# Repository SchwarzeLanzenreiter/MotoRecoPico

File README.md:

# MotoRecoPico

A CAN + GPS data logger for motorcycles. A home-made board carrying a **Raspberry Pi Pico 2
(RP2350)** records the vehicle's CAN bus and GPS to a microSD card. The resulting files open
directly in [MotoRecoViewer](https://github.com/SchwarzeLanzenreiter/MotoRecoViewer).

This is [MotoRecoLogger](https://github.com/SchwarzeLanzenreiter/MotoRecoLogger) — which ran on a
Raspberry Pi plus a HAT — collapsed onto a single board. The recording format is compatible, so old
and new logs read with the same tools.

## Repository layout

| Directory | Contents |
|---|---|
| [`firmware/`](firmware/) | Firmware for the Pico 2 (C / pico-sdk). See [firmware/README.md](firmware/README.md) |
| `cad/kicad/` | KiCad 10 project, fabrication data, generation and inspection scripts |
| `cad/electronics/` | The old EAGLE version (reference only; KiCad is current) |
| [`docs/`](docs/) | Design documents. **[netlist.md](docs/netlist.md) is the canonical description of the circuit** |

## Hardware

| Item | Details |
|---|---|
| Board | 4 layers, 21 × 61 mm, 41 components. The only leaded parts are J1, Y1 and the Pico header |
| MCU | Raspberry Pi Pico 2 (RP2350). Replaceable, in a 2×20 socket. Moved to the back side in v4.2 |
| CAN | Microchip MCP25625 (controller and transceiver in one), driven over SPI1 |
| GPS | YIC GT-502MGG-N. NMEA over UART0 at 9600 bps |
| Storage | microSD (Hirose DM3AT-SF-PEJM5) over SPI0 |
| Vehicle I/F | TE MQS .63, 8 way. Only 5 of them are used: permanent 12V, IG, CAN High, CAN Low, GND |
| Power | 12V → AP63205 buck converter → 5V. The 3.3V rail comes from the Pico's 3V3(OUT) |

**Power is held up for about 0.55 s (measured) after the key goes off.** C13 holds the gate charge
of the high-side switch, and the firmware uses that grace period to close the log. The contract is
in [netlist.md](docs/netlist.md) §4.7.

How the design got here — why four layers, why this placement, what each revision fixed — is
recorded in [netlist.md](docs/netlist.md) and [hardware-design.md](docs/hardware-design.md).
Where to buy the parts is in [parts-sourcing.md](docs/parts-sourcing.md).

## Firmware

- Runs as a **single loop**. There are only two interrupts: CAN reception and the GPS UART
- CAN reception is moved into a ring buffer by the interrupt, so the controller's two-stage FIFO
  does not overflow even when an SD write blocks for hundreds of milliseconds
- NMEA is parsed in-house (replacing gpsd on the Pi version). There is no RTC, so GPS time is
  pinned to the monotonic clock
- FatFs R0.16 is bundled. The SPI block driver for the SD card is our own
- A log is finalized **only on IG OFF detection**. CAN engine speed is not used, to keep
  vehicle-specific knowledge out of the firmware
- The time zone is configured through a hidden file `MOTORECO.CFG` on the microSD card (no rebuild)
- The hardware-independent parts (NMEA, encoding, settings, IG decision, clock) **have tests that
  run on a bare Pico 2 or on a PC**

Build instructions, how to read the logs, and troubleshooting are in
[firmware/README.md](firmware/README.md).

## Recording format (`.dat`)

A sequence of fixed-length 16-byte records. No header, no delimiters, everything little-endian.

| Offset | Type | Contents |
|---|---|---|
| 0 | `uint32` | Seconds since the log started |
| 4 | `uint16` | Milliseconds within that second |
| 6 | `uint16` | CAN ID (standard 11-bit) |
| 8 | `uint8[8]` | Payload (zero-padded when DLC is less than 8) |

GPS rides on CAN IDs that cannot exist, as fixed-point values. **`0x7FF`** carries longitude and
latitude, **`0x7FE`** carries altitude and speed. That way CAN and GPS land in one single time
series.

**`0x7FD`** (added for MotoNavi, not written by the Pi version) carries the absolute time of each
fix, since the record time above only counts from the start of the log. One per fix, written when
the fix's GGA sentence arrives and after any `0x7FF` that sentence produced, so it pairs with the
`0x7FF` at or just before it. It is written while standing still too, when `0x7FF` is skipped
because the position has not changed:

| Bytes | Contents |
|---|---|
| 0–5 | UTC of the fix, Unix milliseconds, 48-bit little-endian |
| 6 | Fix kind in the high nibble (0 none, 1 2D, 2 3D, 3 DGPS/SBAS/RTK), satellites used in the low nibble (15 = 15 or more) |
| 7 | HDOP × 10, rounded (255 = 25.5 or more, 0 = not reported) |

The time of day, satellites and HDOP all come from that GGA. GGA has no date, so the date is
taken from the last RMC with a fix, and nothing is written before the first one. GGA rather than
RMC because the receiver sends GSA and GSV between the two on every fifth fix, which made an
RMC-timed frame arrive about 45 ms late on those fixes only.
Readers that do not know `0x7FD` skip it like any other ID.

> This format is a **contract shared with MotoRecoLogger (the Pi version) and MotoRecoViewer**;
> changing it affects all three repositories. `0x7FF`, `0x7FE` and `0x7FD` are reserved in every
> MotoReco repository.

File names are `YYYYMMDD_HHMMSS.dat` (key-off time, local time). The date is unknown until GPS gets
a fix, so recording starts into `TMPnnnnn.DAT` and the file is renamed to the start time once a fix
arrives.

## Status

- **Verified on the bike with both CAN and GPS recording** (2026-09)
- The board is v4.2. Real operation was confirmed on a physical v4.1 board (v4.2 is identical in
  parts, nets and GPIO assignment)
- Not yet confirmed: an end-to-end check of opening a recorded `.dat` in MotoRecoViewer

## Related repositories

- [MotoRecoLogger](https://github.com/SchwarzeLanzenreiter/MotoRecoLogger) — the logger daemon for
  the Raspberry Pi; this firmware was ported from it
- [MotoRecoViewer](https://github.com/SchwarzeLanzenreiter/MotoRecoViewer) — the Windows
  application that views the recorded `.dat` files

## License

MIT License ([LICENSE](LICENSE)).

The bundled ChaN FatFs is covered by its own license
([firmware/third_party/fatfs/LICENSE.txt](firmware/third_party/fatfs/LICENSE.txt)).

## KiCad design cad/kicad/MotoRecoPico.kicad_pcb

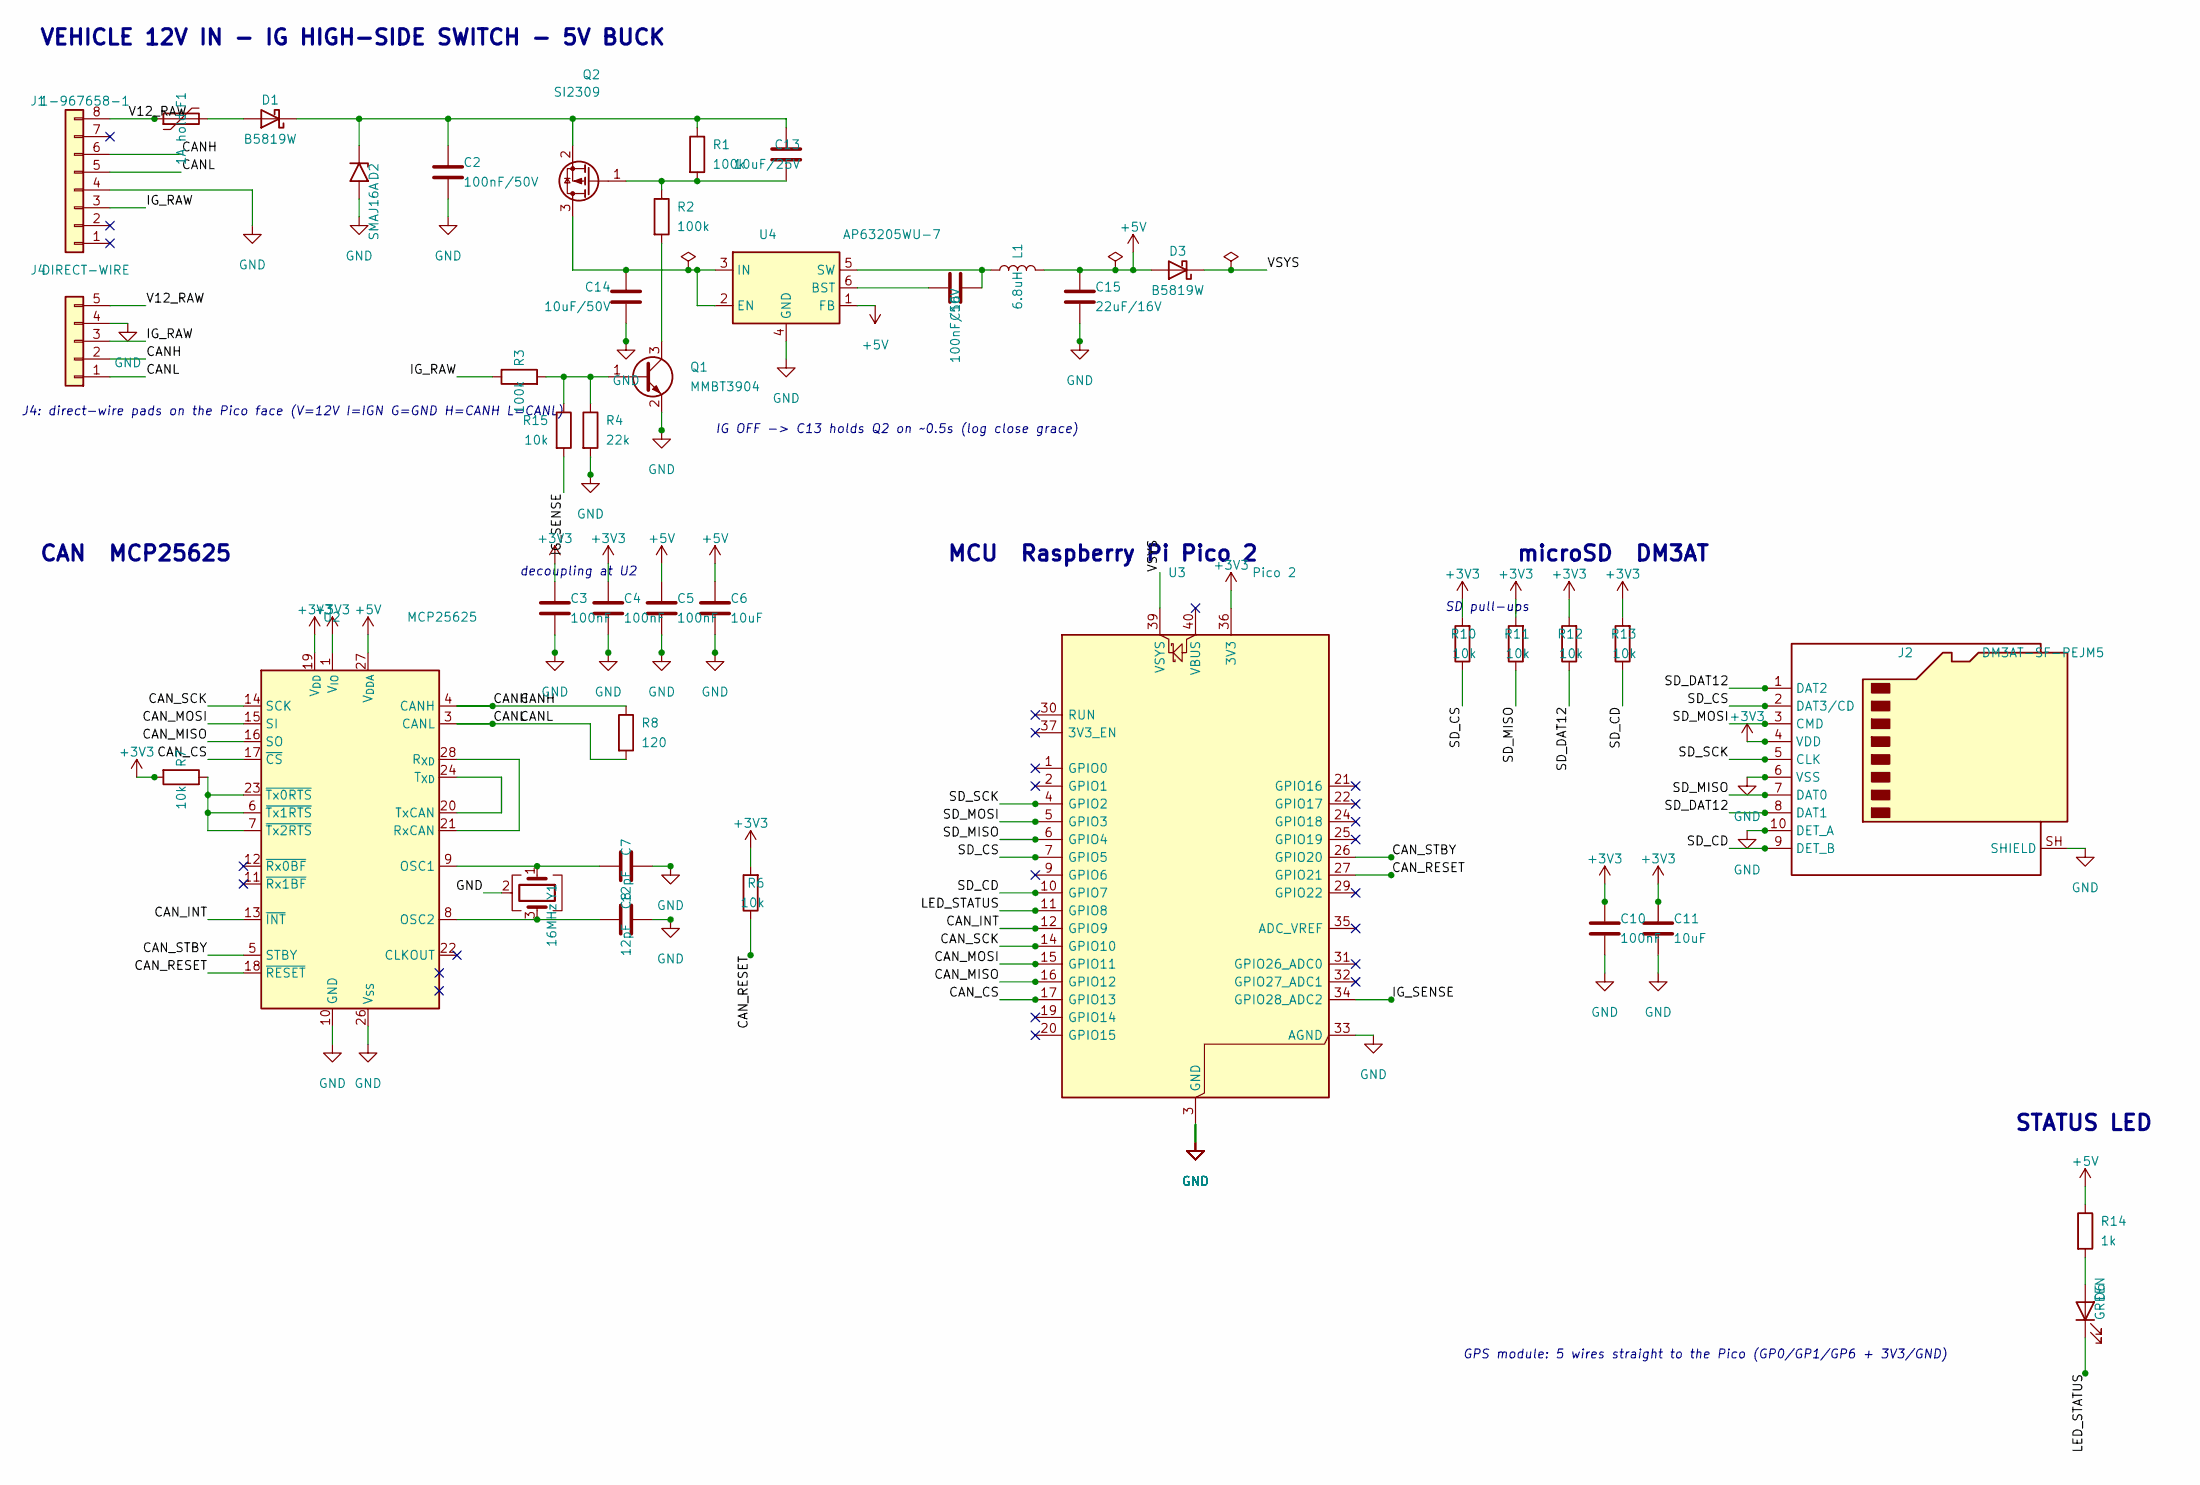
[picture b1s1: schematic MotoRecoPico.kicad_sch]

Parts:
C2, C16: 100nF/50V; C_0603_1608Metric
C3, C4, C5, C10: 100nF; C_0603_1608Metric
C6, C11: 10uF; C_0603_1608Metric
C7, C8: 12pF; C_0603_1608Metric
C13: 10uF/25V; C_0805_2012Metric
C14: 10uF/50V; C_1206_3216Metric
C15: 22uF/16V; C_0805_2012Metric
D1, D3: B5819W; D_SOD-123
D2: SMAJ16A; D_SMA
D6: GREEN; LED-SideView-2.8x1.2
F1: 1A hold; Fuse_1206_3216Metric
J1: 1-967658-1; MQS-8-RA-1-967658-1
J2: DM3AT-SF-PEJM5; microSD_HC_Hirose_DM3AT-SF-PEJM5
J4: DIRECT-WIRE; PAD-5P-DIRECT
L1: 6.8uH; L_Abracon_ASPI-4030S
Q1: MMBT3904; SOT-23
Q2: SI2309; SOT-23
R1, R2, R3: 100k; R_0603_1608Metric
R4: 22k; R_0603_1608Metric
R6, R7, R10, R11, R12, R13, R15: 10k; R_0603_1608Metric
R8: 120; R_0603_1608Metric
R14: 1k; R_0603_1608Metric
U2: MCP25625; SSOP-28_5.3x10.2mm_P0.65mm
U3: Pico 2; Pico2-SMD-Flush
U4: AP63205WU-7; TSOT-23-6
Y1: 16MHz; Crystal_SMD_3225-4Pin_3.2x2.5mm

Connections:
BST_5V: C16.2, U4.6 (BST)
CANH: J1.6, J4.2, R8.1, U2.4 (CANH)
CANL: J1.5, J4.1, R8.2, U2.3 (CANL)
CAN_CS: U2.17 (~CS), U3.17 (GPIO13)
CAN_INT: U2.13 (~INT), U3.12 (GPIO9)
CAN_MISO: U2.16 (SO), U3.16 (GPIO12)
CAN_MOSI: U2.15 (SI), U3.15 (GPIO11)
CAN_RESET: R6.1, U2.18 (~RESET), U3.27 (GPIO21)
CAN_SCK: U2.14 (SCK), U3.14 (GPIO10)
CAN_STBY: U2.5 (STBY), U3.26 (GPIO20)
GND: C2.2, C3.2, C4.2, C5.2, C6.2, C7.2, C8.2, C10.2, C11.2, C14.2, C15.2, D2.2 (A2), J1.4, J2.6 (VSS), J2.10 (DET_A), J2.SH (SHIELD), J4.4, Q1.2 (E), R4.2, U2.10 (GND), U2.26 (V_{SS}), U3.3 (GND), U3.8 (GND), U3.13 (GND), U3.18 (GND), U3.23 (GND), U3.28 (GND), U3.33 (AGND), U3.38 (GND), U4.4 (GND), Y1.2 (G), Y1.4 (G)
IG_RAW: J1.3, J4.3, R3.1
IG_SENSE: R15.2, U3.34 (GPIO28_ADC2)
LED_A: D6.2 (A), R14.2
LED_STATUS: D6.1 (K), U3.11 (GPIO8)
Q1_B: Q1.1 (B), R3.2, R4.1, R15.1
Q1_C: Q1.3 (C), R2.2
Q2_G: C13.1, Q2.1 (G), R1.2, R2.1
RXCAN: U2.21 (RxCAN), U2.28 (R_{XD})
SD_CD: J2.9 (DET_B), R13.1, U3.10 (GPIO7)
SD_CS: J2.2 (DAT3/CD), R10.1, U3.7 (GPIO5)
SD_DAT12: J2.1 (DAT2), J2.8 (DAT1), R12.1
SD_MISO: J2.7 (DAT0), R11.1, U3.6 (GPIO4)
SD_MOSI: J2.3 (CMD), U3.5 (GPIO3)
SD_SCK: J2.5 (CLK), U3.4 (GPIO2)
SW_5V: C16.1, L1.1, U4.5 (SW)
TXCAN: U2.20 (TxCAN), U2.24 (T_{XD})
TXNRTS: R7.1, U2.6 (~Tx1RTS), U2.7 (~Tx2RTS), U2.23 (~Tx0RTS)
V3V3: C3.1, C4.1, C10.1, C11.1, J2.4 (VDD), R6.2, R7.2, R10.2, R11.2, R12.2, R13.2, U2.1 (V_{IO}), U2.19 (V_{DD}), U3.36 (3V3)
V5: C5.1, C6.1, C15.1, D3.2 (A), L1.2, R14.1, U2.27 (V_{DDA}), U4.1 (FB)
V12P: C2.1, C13.2, D1.1 (K), D2.1 (A1), Q2.2 (S), R1.1
V12_FUSED: D1.2 (A), F1.2
V12_RAW: F1.1, J1.8, J4.5
V12_SW: C14.1, Q2.3 (D), U4.2 (EN), U4.3 (IN)
VSYS: D3.1 (K), U3.39 (VSYS)
XTAL1: C7.1, U2.9 (OSC1), Y1.1
XTAL2: C8.1, U2.8 (OSC2), Y1.3

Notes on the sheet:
VEHICLE 12V IN - IG HIGH-SIDE SWITCH - 5V BUCK
CAN MCP25625
MCU Raspberry Pi Pico 2
microSD DM3AT
STATUS LED
IG OFF -> C13 holds Q2 on ~0.5s (log close grace)
decoupling at U2
SD pull-ups
J4: direct-wire pads on the Pico face (V=12V I=IGN G=GND H=CANH L=CANL)
GPS module: 5 wires straight to the Pico (GP0/GP1/GP6 + 3V3/GND)

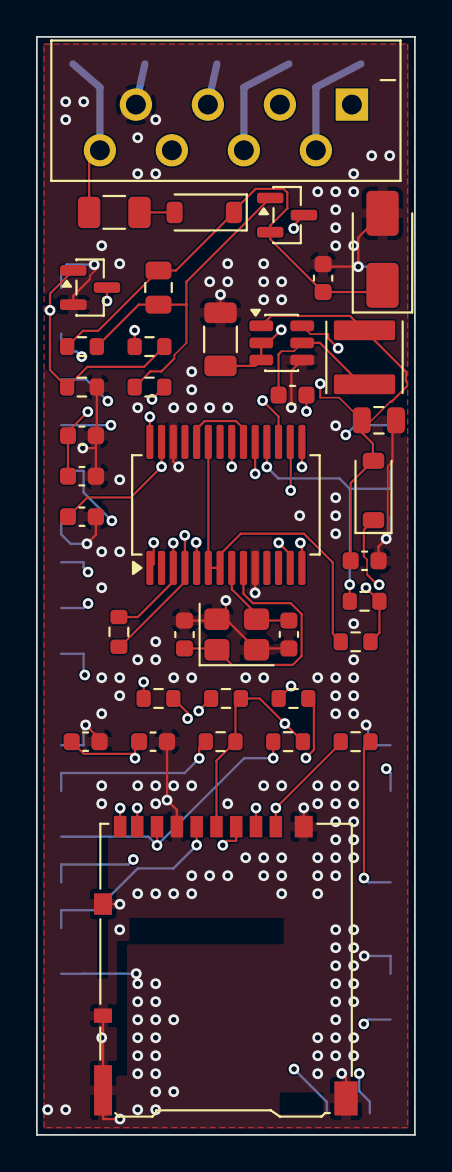
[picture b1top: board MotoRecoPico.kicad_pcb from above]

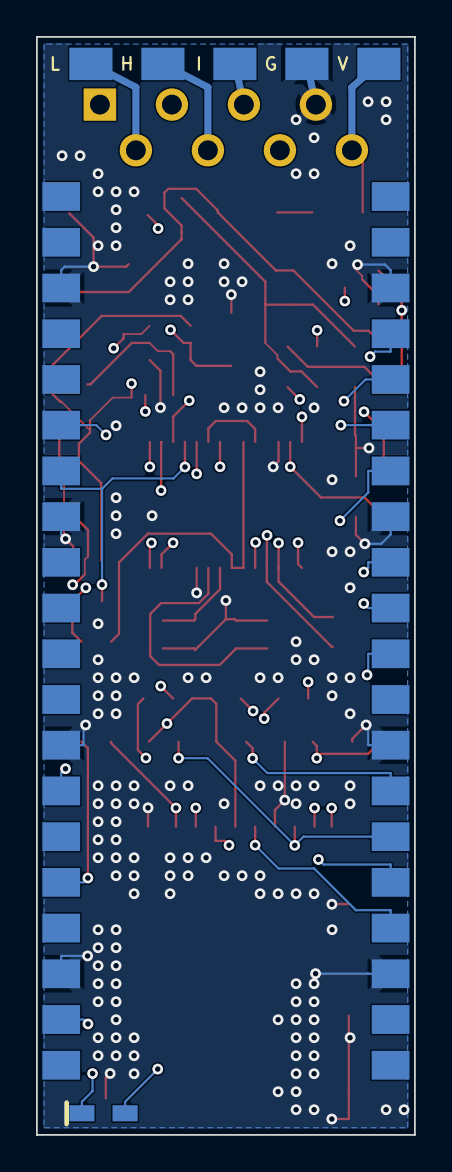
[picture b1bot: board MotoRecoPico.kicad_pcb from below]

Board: 4 copper layers, 21.0 x 61.0 mm, 41 parts (3 on the bottom side), 37 nets.

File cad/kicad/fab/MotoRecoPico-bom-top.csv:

"Designator","Comment","Footprint","Qty","LCSC Part #"
"C2","100nF/50V","Capacitor_SMD:C_0603_1608Metric","1","C14663"
"C3","100nF","Capacitor_SMD:C_0603_1608Metric","1","C14663"
"C4","100nF","Capacitor_SMD:C_0603_1608Metric","1","C14663"
"C5","100nF","Capacitor_SMD:C_0603_1608Metric","1","C14663"
"C6","10uF","Capacitor_SMD:C_0603_1608Metric","1","C19702"
"C7","12pF","Capacitor_SMD:C_0603_1608Metric","1",""
"C8","12pF","Capacitor_SMD:C_0603_1608Metric","1",""
"C10","100nF","Capacitor_SMD:C_0603_1608Metric","1","C14663"
"C11","10uF","Capacitor_SMD:C_0603_1608Metric","1","C19702"
"C13","10uF/25V","Capacitor_SMD:C_0805_2012Metric","1",""
"C14","10uF/50V","Capacitor_SMD:C_1206_3216Metric","1",""
"C15","22uF/16V","Capacitor_SMD:C_0805_2012Metric","1",""
"C16","100nF/50V","Capacitor_SMD:C_0603_1608Metric","1","C14663"
"D1","B5819W","Diode_SMD:D_SOD-123","1","C8598"
"D2","SMAJ16A","Diode_SMD:D_SMA","1","C74561"
"D3","B5819W","Diode_SMD:D_SOD-123","1","C8598"
"F1","1A hold","Fuse:Fuse_1206_3216Metric","1","C3761685"
"J2","DM3AT-SF-PEJM5","Connector_Card:microSD_HC_Hirose_DM3AT-SF-PEJM5","1",""
"L1","6.8uH","Inductor_SMD:L_Abracon_ASPI-4030S","1","C62684"
"Q1","MMBT3904","Package_TO_SOT_SMD:SOT-23","1","C20526"
"Q2","SI2309","Package_TO_SOT_SMD:SOT-23","1","C10493"
"R1","100k","Resistor_SMD:R_0603_1608Metric","1","C25803"
"R2","100k","Resistor_SMD:R_0603_1608Metric","1","C25803"
"R3","100k","Resistor_SMD:R_0603_1608Metric","1","C25803"
"R4","22k","Resistor_SMD:R_0603_1608Metric","1","C31850"
"R6","10k","Resistor_SMD:R_0603_1608Metric","1","C25804"
"R7","10k","Resistor_SMD:R_0603_1608Metric","1","C25804"
"R8","120","Resistor_SMD:R_0603_1608Metric","1","C22787"
"R10","10k","Resistor_SMD:R_0603_1608Metric","1","C25804"
"R11","10k","Resistor_SMD:R_0603_1608Metric","1","C25804"
"R12","10k","Resistor_SMD:R_0603_1608Metric","1","C25804"
"R13","10k","Resistor_SMD:R_0603_1608Metric","1","C25804"
"R14","1k","Resistor_SMD:R_0603_1608Metric","1","C21190"
"R15","10k","Resistor_SMD:R_0603_1608Metric","1","C25804"
"U2","MCP25625","Package_SO:SSOP-28_5.3x10.2mm_P0.65mm","1","C184944"
"U4","AP63205WU-7","Package_TO_SOT_SMD:TSOT-23-6","1","C2071056"
"Y1","16MHz","Crystal:Crystal_SMD_3225-4Pin_3.2x2.5mm","1","C13738"

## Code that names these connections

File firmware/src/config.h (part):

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// ---------------------------------------------------------------------------

// microSD on SPI0
#define PIN_SD_SCK		2
#define PIN_SD_MOSI		3
#define PIN_SD_MISO		4
#define PIN_SD_CS		5	// driven as plain GPIO, not the SPI hardware CSn
#define PIN_SD_CD		7	// card detect switch, external 10k pull up (R13)

// GPS GT-502MGG-N on UART0
#define PIN_GPS_TX		0	// pico -> module RXD (green wire)
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#define PIN_LED			8

// CAN controller MCP25625 on SPI1
#define PIN_CAN_INT		9	// active low, open drain on the MCP25625 side
#define PIN_CAN_SCK		10
#define PIN_CAN_MOSI	11
#define PIN_CAN_MISO	12
#define PIN_CAN_CS		13	// driven as plain GPIO, not the SPI hardware CSn
#define PIN_CAN_STBY	20	// high puts the transceiver in standby
#define PIN_CAN_RESET	21	// active low, has a 10k pull up (R6)

// ignition sense. unchanged by the v4.1 rotation
#define PIN_IG_SENSE	28
#define IG_ADC_INPUT	2	// GP28 is ADC2

// GP14 to GP19, GP22, GP26 and GP27 are tied to GND on this board. never drive them
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
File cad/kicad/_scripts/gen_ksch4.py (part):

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    ('U2', '9'), ('Y1', '1'), ('C7', '1'), ('U2', '8'), ('Y1', '2'), ('C8', '1'),
    ('R14', '2'), ('D6', '2'),
}
# labels dropped onto hand wires (net, x, y, angle) - CANH/CANL reach J1 by
# name, VSYS reaches the Pico
HAND_LABELS = [
    ('CANH', 74, 99, 0, 'left'), ('CANL', 74, 101, 0, 'left'),
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    HANDLED.update({('Y1', '3'), ('Y1', '2'), ('Y1', '4')})
    HAND_LABELS.append(('GND', 70, 120, 0, 'right'))
    # J4 connects purely by name: its stubs are auto-labelled, so the J1-F1
    # wire needs the matching label to merge into one V12_RAW net
    HAND_LABELS.append(('V12_RAW', 30, 33, 0, 'left'))
    NOTES.append(("J4: direct-wire pads on the Pico face (V=12V I=IGN G=GND H=CANH L=CANL)", 18, 66))
    HAND_POWER[:] = [hp for hp in HAND_POWER
                     if (hp[1], hp[2]) not in ((281, 166), (290, 151))]
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

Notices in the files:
firmware/src/config.h:
Copyright (c) 2026 Schwarze Lanzenreiter
